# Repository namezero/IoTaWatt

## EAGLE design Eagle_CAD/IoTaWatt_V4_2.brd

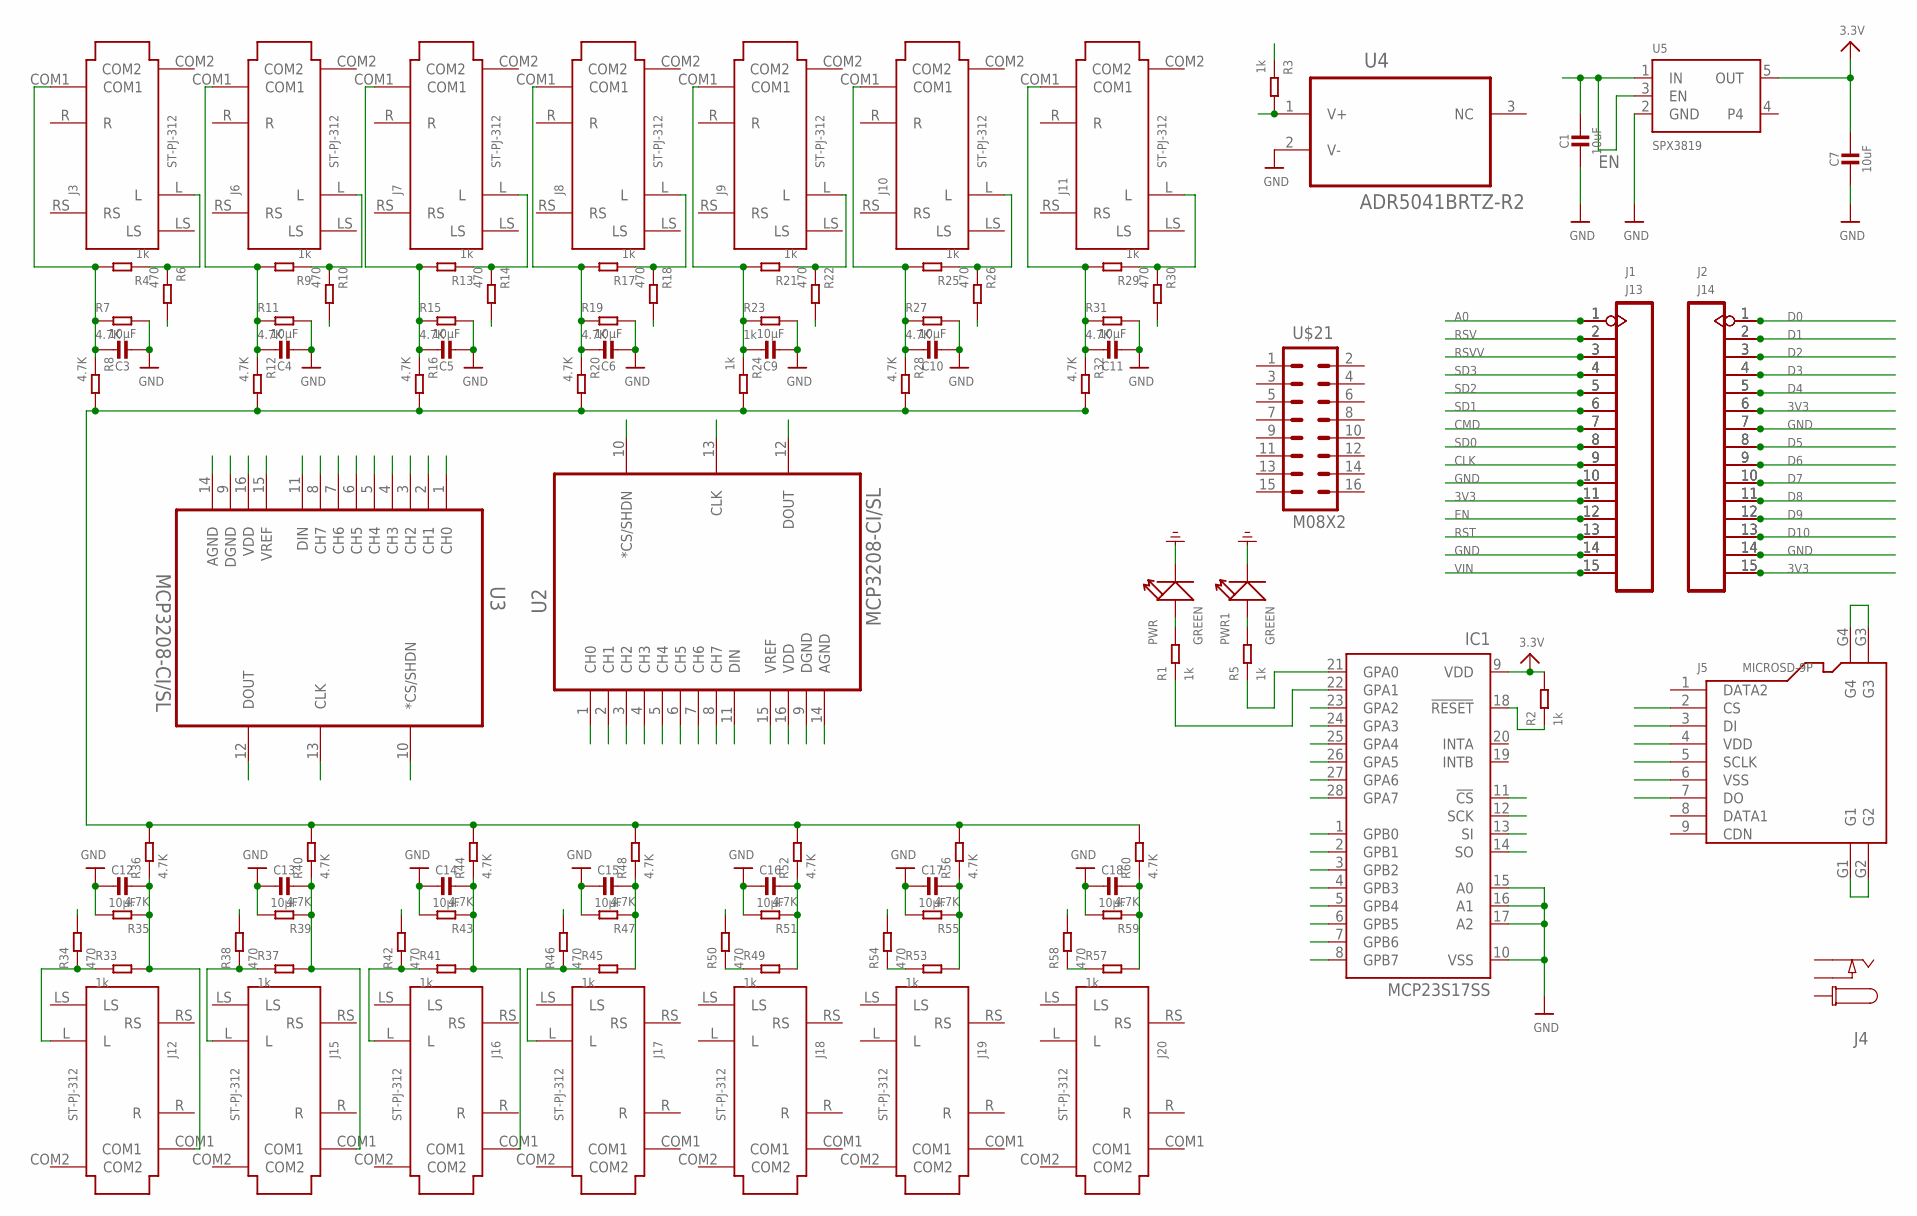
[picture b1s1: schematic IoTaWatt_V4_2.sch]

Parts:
C1, C7: 10uF; 0603-NO
C3, C4, C5, C6, C9, C10, C11, C12, C13, C14, C15, C16, C17, C18: 10µF; 0805-NO
IC1: MCP23S17SS; SSOP28
J1, J2, J13, J14: HEADER-15P'2.54'; H15-2.54
J3, J6, J7, J8, J9, J10, J11, J12, J15, J16, J17, J18, J19, J20: ST-PJ-312; AUDIO6P-SMD-3.5-14.0X6.4X5.0MM
J4: CON_DC_M-DC_SMD; DC_BARREL_JACK_SMD_2MM
J5: MICROSD-9P; MICRO-SD9+4P-SMD-16.1X14.5X1.85MM
PWR, PWR1: GREEN; LED-0603
R1, R2, R3, R4, R5, R9, R13, R17, R21, R23, R24, R25, R29, R33, R37, R41, R45, R49, R53, R57: 1k; R0603
R6, R10, R14, R18, R22, R26, R30, R34, R38, R42, R46, R50, R54, R58: 470; R0603
R7, R8, R11, R12, R15, R16, R19, R20, R27, R28, R31, R32, R35, R36, R39, R40, R43, R44, R47, R48, R51, R52, R55, R56, R59, R60: 4.7K; R0603
U2, U3: MCP3208-CI/SL; SOIC127P600X175-16N
U4: ADR5041BRTZ-R2; SOT95P237X112-3N
U5: SPX3819; SOT23-5
U$21: M08X2; 2X8

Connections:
3V3: C7.1, IC1.9 (VDD), J1.11, J2.6, J2.15, J5.4 (VDD), J13.11, J14.6, J14.15, R2.2, U5.5 (OUT)
A0: J1.1, J13.1
CLK: J1.9, J13.9
CMD: J1.7, J13.7
D0: J2.1, J14.1
D1: J2.2, J14.2
D2: J2.3, J14.3
D3: J2.4, J14.4
D4: J2.5, J14.5
D5: J2.8, J5.5 (SCLK), J14.8
D6: J2.9, J5.7 (DO), J14.9
D7: J2.10, J5.3 (DI), J14.10
D8: J2.11, J5.2 (CS), J14.11
D9: J2.12, J14.12
D10: J2.13, J14.13
EN: C1.1, J1.12, J13.12, U5.1 (IN), U5.3 (EN)
GND: C1.2, C3.2, C4.2, C5.2, C6.2, C7.2, C9.2, C10.2, C11.2, C12.2, C13.2, C14.2, C15.2, C16.2, C17.2, C18.2, IC1.10 (VSS), IC1.15 (A0), IC1.16 (A1), IC1.17 (A2), J1.10, J1.14, J2.7, J2.14, J5.6 (VSS), J13.10, J13.14, J14.7, J14.14, PWR.-, PWR1.-, R7.2, R11.2, R15.2, R19.2, R23.2, R27.2, R31.2, R35.2, R39.2, R43.2, R47.2, R51.2, R55.2, R59.2, U4.2 (V-), U5.2 (GND)
unnamed: PWR.+, R1.2
unnamed: PWR1.+, R5.2
unnamed: IC1.21 (GPA0), R5.1
unnamed: IC1.22 (GPA1), R1.1
unnamed: C3.1, J3.COM1, R4.2, R7.1, R8.1
unnamed: J3.L, R4.1, R6.1
unnamed: R3.2, U4.1 (V+)
unnamed: C4.1, J6.COM1, R9.2, R11.1, R12.1
unnamed: J6.L, R9.1, R10.1
unnamed: J5.G1, J5.G2
unnamed: C5.1, J7.COM1, R13.2, R15.1, R16.1
unnamed: J7.L, R13.1, R14.1
unnamed: J5.G3, J5.G4
unnamed: C6.1, J8.COM1, R17.2, R19.1, R20.1
unnamed: J8.L, R17.1, R18.1
unnamed: R8.2, R12.2, R16.2, R20.2, R24.2, R28.2, R32.2, R36.2, R40.2, R44.2, R48.2, R52.2, R56.2, R60.2
unnamed: C9.1, J9.COM1, R21.2, R23.1, R24.1
unnamed: J9.L, R21.1, R22.1
unnamed: C10.1, J10.COM1, R25.2, R27.1, R28.1
unnamed: J10.L, R25.1, R26.1
unnamed: C11.1, J11.COM1, R29.2, R31.1, R32.1
unnamed: J11.L, R29.1, R30.1
unnamed: C12.1, J12.COM1, R33.2, R35.1, R36.1
unnamed: J12.L, R33.1, R34.1
unnamed: C13.1, J15.COM1, R37.2, R39.1, R40.1
unnamed: J15.L, R37.1, R38.1
unnamed: C14.1, J16.COM1, R41.2, R43.1, R44.1
unnamed: J16.L, R41.1, R42.1
unnamed: C15.1, R45.2, R47.1, R48.1
unnamed: J17.L, R45.1, R46.1
unnamed: C16.1, R49.2, R51.1, R52.1
unnamed: R49.1, R50.1
unnamed: C17.1, R53.2, R55.1, R56.1
unnamed: R53.1, R54.1
unnamed: C18.1, R57.2, R59.1, R60.1
unnamed: R57.1, R58.1
unnamed: IC1.18 (!RESET), R2.1
RST: J1.13, J13.13
RSV: J1.2, J13.2
RSVV: J1.3, J13.3
SD0: J1.8, J13.8
SD1: J1.6, J13.6
SD2: J1.5, J13.5
SD3: J1.4, J13.4
VIN: J1.15, J13.15

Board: 2 copper layers, 104 parts (8 on the bottom side), 62 nets, no tracks yet.

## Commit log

2016-12-30 Added Eagle format schematic and board layout

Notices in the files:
parts and their libraries:
microbuilder: This work is placed in the public domain, and may be freely used for commercial and non-commercial work with the following conditions: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
SparkFun-Connectors: Licensing: Creative Commons ShareAlike 4.0 International - https://creativecommons.org/licenses/by-sa/4.0
